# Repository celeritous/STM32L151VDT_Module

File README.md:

# STM32L151VDT_Module
This repository is for an STM32L151/152 Cortex M3 32bit low power ARM  processor module. The design supports any of the STM32L151 or 152 processors in the QFP100 package. It is designed primarily for battery powered applications. 

The design is in KiCad and is released under the CERN OHL Ver 1.2 It is on a 50mm x 50mm 4 layer PCB with two 38 Pin dual row 100mil headers for user power and IO. There is no on-board voltage regulation so the user must supply regulated 1.8V-3.3V power to the board. Voltages in excess of this may damage the board. The board may operate as low as 1.65V but not all peripherals will operate at this voltage and full clock speed maynot be supported. The processor is capable of internal cclock speeds of up to 32MHz. 

Features include a USB FS port that can function as host or client as well as and optional uSD card slot and ESP-07 serial WiFi Module. The uSD card slot and WiFi module may be independently powered down by the processor to reduce power consumption. 

Along with the hardware design, the repository also contains a sample STM32CubeMX pin assignemt project file and a sample Atollic TrueStudio project file generated by the STM32CubeMX project file.

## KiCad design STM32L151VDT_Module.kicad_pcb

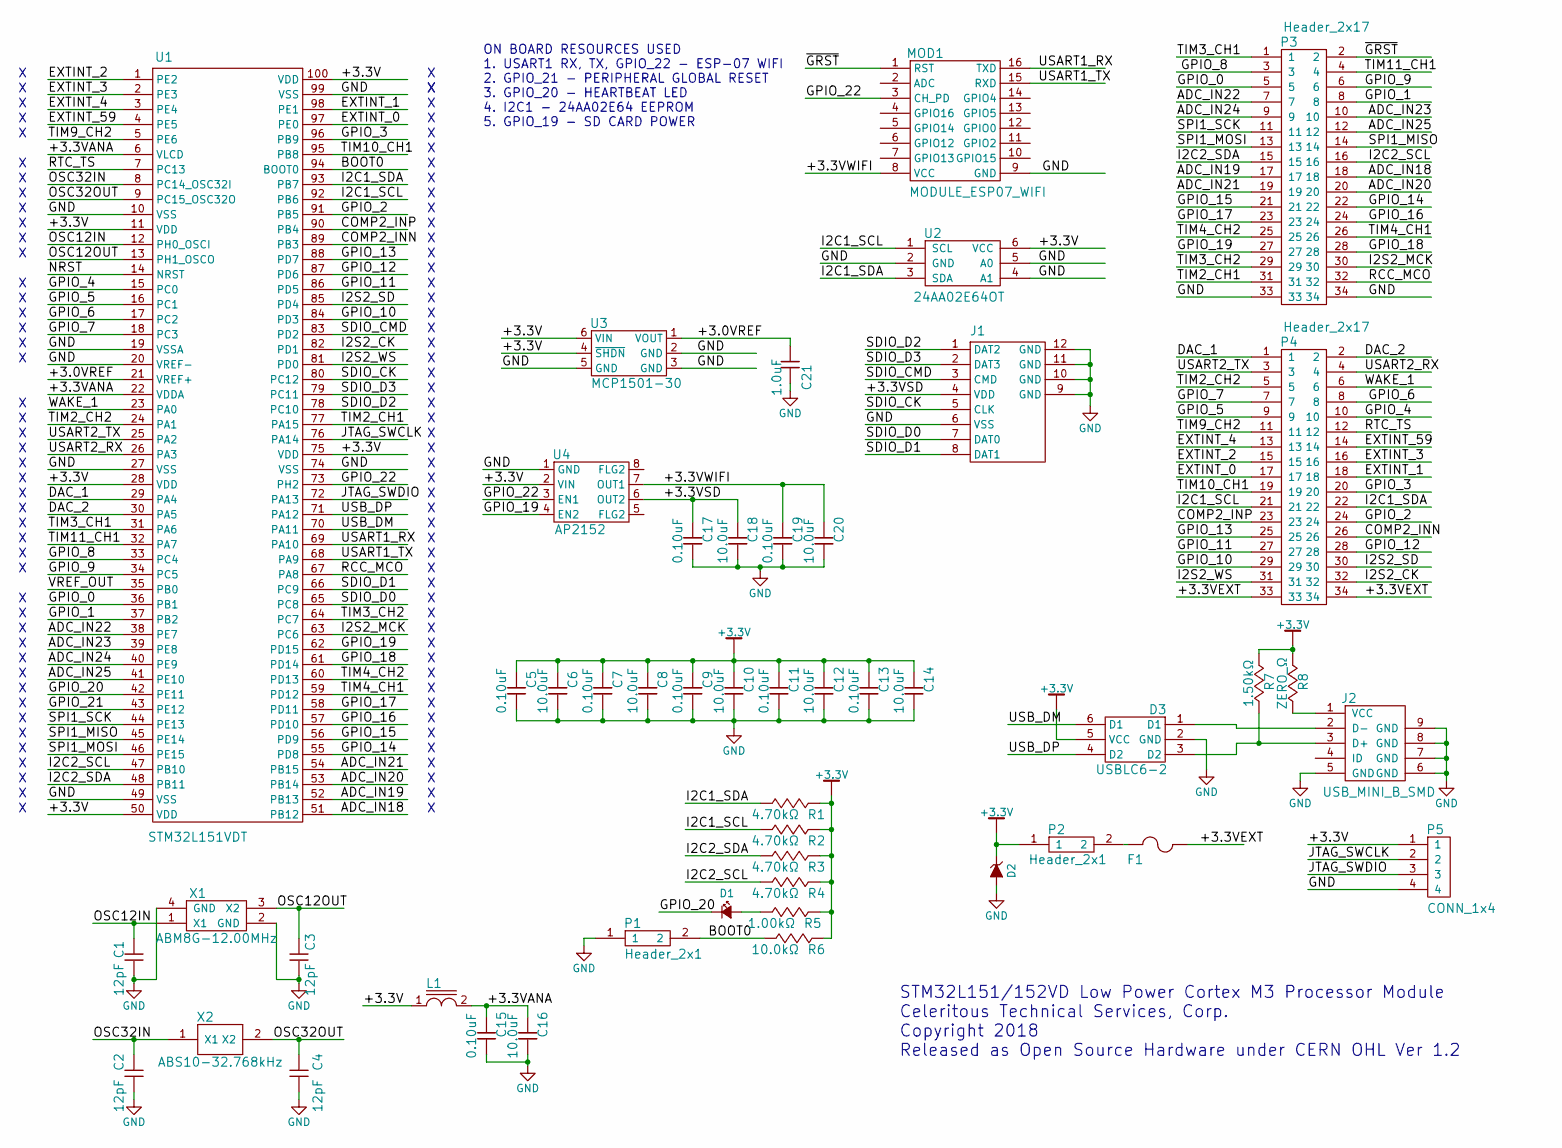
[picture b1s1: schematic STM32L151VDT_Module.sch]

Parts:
C1, C2, C3, C4: 12pF; P0603
C5, C7, C9, C11, C13, C15, C17, C19: 0.10uF; P0603
C6, C8, C10, C12, C14, C16, C18, C20: 10.0uF; P0603
C21: 1.0uF; P0603
D1: Led_Small; D0805
D2: SMLJ33ABCT; SOD128
D3: USBLC6-2; SOT23-6
F1: FUSE_PTC_.5A_33V; P1812
J1: SOCKET_MICRO_SD_SMT_3M; CONN_SDMICRO_3M
J2: USB_MINI_B_SMD; CONN_USB_UX60-MB
L1: FERRITE_BEAD; P0603
MOD1: MODULE_ESP07_WIFI
P1, P2: Header_2x1; Header_2x1_Shrouded_100mil
P3, P4: Header_2x17; Header_2x17_Shrouded_100mil
P5: CONN_1x4; Connector_1x4_100mil_TH
R1, R2, R3, R4: 4.70kΩ; P0603
R5: 1.00kΩ; P0603
R6: 10.0kΩ; P0603
R7: 1.50kΩ; P0603
R8: ZERO_Ω; P0603
U1: STM32L151VDT; QFP_100_14X14_0.5
U2: 24AA02E64OT; SOT23-6
U3: MCP1501-30; SOT23-6
U4: AP2152; SOIC_8
X1: ABM8G-12.00MHz; XTAL_3.2X2.5
X2: ABS10-32.768kHz; XTAL_1.8X4.9mm

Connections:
+3.3V: C5.1, C6.1, C7.1, C8.1, C9.1, C10.1, C11.1, C12.1, C13.1, C14.1, D2.K, D3.5 (VCC), L1.1, P2.1, P5.1, R1.2, R2.2, R3.2, R4.2, R5.2, R6.2, R7.1, R8.1, U1.11 (VDD), U1.28 (VDD), U1.50 (VDD), U1.75 (VDD), U1.100 (VDD), U2.6 (VCC), U3.4 (~SHDN), U3.6 (VIN), U4.2 (VIN)
/+3.0VREF: C21.1, U1.21 (VREF+), U3.1 (VOUT)
/+3.3VANA: C15.1, C16.1, L1.2, U1.6 (VLCD), U1.22 (VDDA)
/+3.3VEXT: F1.2, P4.33, P4.34
/+3.3VSD: C17.1, C18.1, J1.4 (VDD), U4.6 (OUT2)
/+3.3VWIFI: C19.1, C20.1, MOD1.8 (VCC), U4.7 (OUT1)
/ADC_IN18: P3.18, U1.51 (PB12)
/ADC_IN19: P3.17, U1.52 (PB13)
/ADC_IN20: P3.20, U1.53 (PB14)
/ADC_IN21: P3.19, U1.54 (PB15)
/ADC_IN22: P3.7, U1.38 (PE7)
/ADC_IN23: P3.10, U1.39 (PE8)
/ADC_IN24: P3.9, U1.40 (PE9)
/ADC_IN25: P3.12, U1.41 (PE10)
/BOOT0: P1.2, R6.1, U1.94 (BOOT0)
/COMP2_INN: P4.26, U1.89 (PB3)
/COMP2_INP: P4.23, U1.90 (PB4)
/DAC_1: P4.1, U1.29 (PA4)
/DAC_2: P4.2, U1.30 (PA5)
/EXTINT_0: P4.17, U1.97 (PE0)
/EXTINT_1: P4.18, U1.98 (PE1)
/EXTINT_2: P4.15, U1.1 (PE2)
/EXTINT_3: P4.16, U1.2 (PE3)
/EXTINT_4: P4.13, U1.3 (PE4)
/EXTINT_59: P4.14, U1.4 (PE5)
/GPIO_0: P3.5, U1.36 (PB1)
/GPIO_1: P3.8, U1.37 (PB2)
/GPIO_2: P4.24, U1.91 (PB5)
/GPIO_3: P4.20, U1.96 (PB9)
/GPIO_4: P4.10, U1.15 (PC0)
/GPIO_5: P4.9, U1.16 (PC1)
/GPIO_6: P4.8, U1.17 (PC2)
/GPIO_7: P4.7, U1.18 (PC3)
/GPIO_8: P3.3, U1.33 (PC4)
/GPIO_9: P3.6, U1.34 (PC5)
/GPIO_10: P4.29, U1.84 (PD3)
/GPIO_11: P4.27, U1.86 (PD5)
/GPIO_12: P4.28, U1.87 (PD6)
/GPIO_13: P4.25, U1.88 (PD7)
/GPIO_14: P3.22, U1.55 (PD8)
/GPIO_15: P3.21, U1.56 (PD9)
/GPIO_16: P3.24, U1.57 (PD10)
/GPIO_17: P3.23, U1.58 (PD11)
/GPIO_18: P3.28, U1.61 (PD14)
/GPIO_19: P3.27, U1.62 (PD15), U4.4 (EN2)
/GPIO_20: D1.K, U1.42 (PE11)
/GPIO_22: MOD1.3 (CH_PD), U1.73 (PH2), U4.3 (EN1)
/I2C1_SCL: P4.21, R2.1, U1.92 (PB6), U2.1 (SCL)
/I2C1_SDA: P4.22, R1.1, U1.93 (PB7), U2.3 (SDA)
/I2C2_SCL: P3.16, R4.1, U1.47 (PB10)
/I2C2_SDA: P3.15, R3.1, U1.48 (PB11)
/I2S2_CK: P4.32, U1.82 (PD1)
/I2S2_MCK: P3.30, U1.63 (PC6)
/I2S2_SD: P4.30, U1.85 (PD4)
/I2S2_WS: P4.31, U1.81 (PD0)
/JTAG_SWCLK: P5.2, U1.76 (PA14)
/JTAG_SWDIO: P5.3, U1.72 (PA13)
/OSC12IN: C1.1, U1.12 (PH0_OSCI), X1.1 (X1)
/OSC12OUT: C3.1, U1.13 (PH1_OSCO), X1.3 (X2)
/OSC32IN: C2.1, U1.8 (PC14_OSC32I), X2.1 (X1)
/OSC32OUT: C4.1, U1.9 (PC15_OSC32O), X2.2 (X2)
/RCC_MCO: P3.32, U1.67 (PA8)
/RTC_TS: P4.12, U1.7 (PC13)
/SDIO_CK: J1.5 (CLK), U1.80 (PC12)
/SDIO_CMD: J1.3 (CMD), U1.83 (PD2)
/SDIO_D0: J1.7 (DAT0), U1.65 (PC8)
/SDIO_D1: J1.8 (DAT1), U1.66 (PC9)
/SDIO_D2: J1.1 (DAT2), U1.78 (PC10)
/SDIO_D3: J1.2 (DAT3), U1.79 (PC11)
/SPI1_MISO: P3.14, U1.45 (PE14)
/SPI1_MOSI: P3.13, U1.46 (PE15)
/SPI1_SCK: P3.11, U1.44 (PE13)
/TIM2_CH1: P3.31, U1.77 (PA15)
/TIM2_CH2: P4.5, U1.24 (PA1)
/TIM3_CH1: P3.1, U1.31 (PA6)
/TIM3_CH2: P3.29, U1.64 (PC7)
/TIM4_CH1: P3.26, U1.59 (PD12)
/TIM4_CH2: P3.25, U1.60 (PD13)
/TIM9_CH2: P4.11, U1.5 (PE6)
/TIM10_CH1: P4.19, U1.95 (PB8)
/TIM11_CH1: P3.4, U1.32 (PA7)
/USART1_RX: MOD1.16 (TXD), U1.69 (PA10)
/USART1_TX: MOD1.15 (RXD), U1.68 (PA9)
/USART2_RX: P4.4, U1.26 (PA3)
/USART2_TX: P4.3, U1.25 (PA2)
/USB_DM: D3.6 (D1), U1.70 (PA11)
/USB_DP: D3.4 (D2), U1.71 (PA12)
/WAKE_1: P4.6, U1.23 (PA0)
/~GRST: MOD1.1 (RST), P3.2
GND: C1.2, C2.2, C3.2, C4.2, C5.2, C6.2, C7.2, C8.2, C9.2, C10.2, C11.2, C12.2, C13.2, C14.2, C15.2, C16.2, C17.2, C18.2, C19.2, C20.2, C21.2, D2.A, D3.2 (GND), J1.6 (VSS), J1.9 (GND), J1.10 (GND), J1.11 (GND), J1.12 (GND), J2.5 (GND), J2.6 (GND), J2.7 (GND), J2.8 (GND), J2.9 (GND), MOD1.9 (GND), P1.1, P3.33, P3.34, P5.4, U1.10 (VSS), U1.19 (VSSA), U1.20 (VREF-), U1.27 (VSS), U1.49 (VSS), U1.74 (VSS), U1.99 (VSS), U2.2 (GND), U2.4 (A1), U2.5 (A0), U3.2 (GND), U3.3 (GND), U3.5 (GND), U4.1 (GND), X1.2 (GND), X1.4 (GND)
unnamed: D1.A, R5.1
unnamed: D3.1 (D1), J2.2 (D-)
unnamed: D3.3 (D2), J2.3 (D+), R7.2
unnamed: F1.1, P2.2
unnamed: J2.1 (VCC), R8.2

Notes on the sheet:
ON BOARD RESOURCES USED 1. USART1 RX, TX, GPIO_22 - ESP-07 WIFI 2. GPIO_21 - PERIPHERAL GLOBAL RESET 3. GPIO_20 - HEARTBEAT LED 4. I2C1 - 24AA02E64 EEPROM 5. GPIO_19 - SD CARD POWER
STM32L151/152VD Low Power Cortex M3 Processor Module Celeritous Technical Services, Corp. Copyright 2018 Released as Open Source Hardware under CERN OHL Ver 1.2

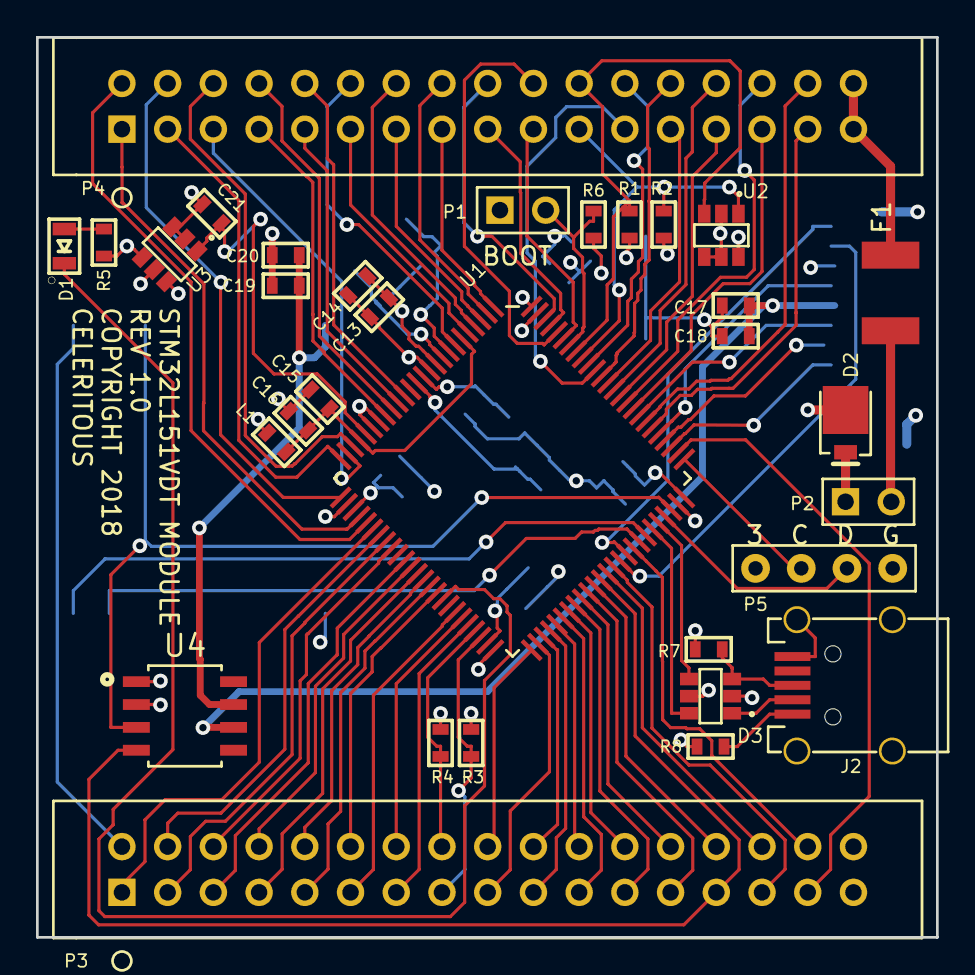
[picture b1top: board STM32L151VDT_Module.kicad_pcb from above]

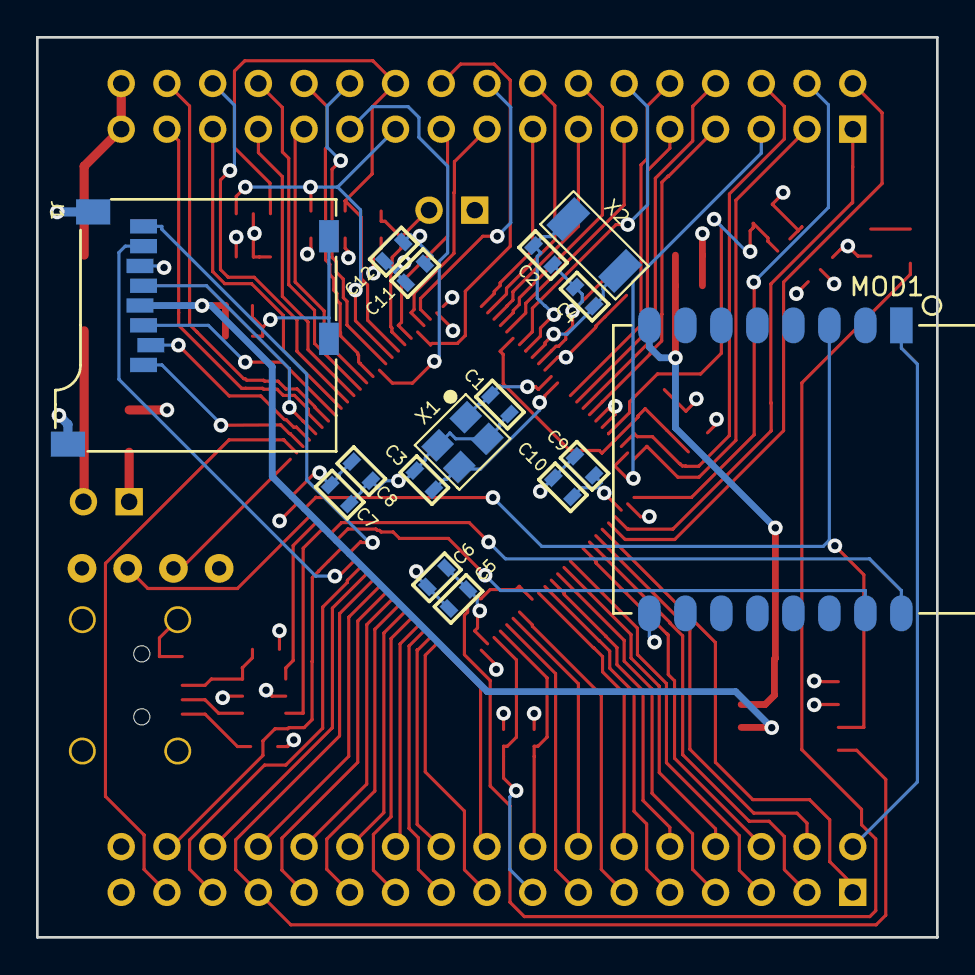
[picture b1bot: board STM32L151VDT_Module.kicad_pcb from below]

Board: 4 copper layers, 50.0 x 50.0 mm, 48 parts (16 on the bottom side), 95 nets.

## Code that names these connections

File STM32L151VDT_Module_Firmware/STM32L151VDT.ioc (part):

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Mcu.Name=STM32L151VDTx
Mcu.Package=LQFP100
Mcu.UserName=STM32L151VDTx
PA0-WKUP1.GPIOParameters=GPIO_Label
PA0-WKUP1.GPIO_Label=WAKE_1
PA0-WKUP1.Mode=SYS_WakeUp0
PA0-WKUP1.Signal=SYS_WKUP1
PA1.Signal=S_TIM2_CH2
PA10.Mode=Asynchronous
PA10.Signal=USART1_RX
PA11.Mode=Device
PA11.Signal=USB_DM
PA12.Mode=Device
PA12.Signal=USB_DP
PA13.Mode=Serial_Wire
PA13.Signal=SYS_JTMS-SWDIO
PA14.Mode=Serial_Wire
PA14.Signal=SYS_JTCK-SWCLK
PA15.Signal=S_TIM2_CH1_ETR
PA2.Mode=Asynchronous
PA2.Signal=USART2_TX
PA3.Mode=Asynchronous
PA3.Signal=USART2_RX
PA4.Signal=COMP_DAC1_group
PA5.Signal=COMP_DAC2_group
PA6.Signal=S_TIM3_CH1
PA7.Signal=S_TIM11_CH1
PA8.Mode=Clock-out
PA8.Signal=RCC_MCO
PA9.Mode=Asynchronous
PA9.Signal=USART1_TX
PB0.GPIOParameters=GPIO_Label
PB0.GPIO_Label=VREF_OUT
PB0.Mode=Voltage_reference
PB0.Signal=SYS_V_REF_OUT
PB1.GPIOParameters=GPIO_Label
PB1.GPIO_Label=GPIO_0
PB1.Signal=GPIO_Input
PB10.Mode=I2C
PB10.Signal=I2C2_SCL
PB11.Mode=I2C
PB11.Signal=I2C2_SDA
PB12.Mode=IN18
PB12.Signal=ADC_IN18
PB13.Mode=IN19
PB13.Signal=ADC_IN19
PB14.Mode=IN20
PB14.Signal=ADC_IN20
PB15.Mode=IN21
PB15.Signal=ADC_IN21
PB2.GPIOParameters=GPIO_Label
PB2.GPIO_Label=GPIO_1
PB2.Signal=GPIO_Input
PB3.GPIOParameters=GPIO_Label
PB3.GPIO_Label=COMP2_INN
PB3.Mode=INM
PB3.Signal=COMP2_INM
PB4.GPIOParameters=GPIO_Label
PB4.GPIO_Label=COMP2_INP
PB4.Mode=INP
PB4.Signal=COMP2_INP
PB5.GPIOParameters=GPIO_Label
PB5.GPIO_Label=GPIO_2
PB5.Signal=GPIO_Input
PB6.Mode=I2C
PB6.Signal=I2C1_SCL
PB7.Mode=I2C
PB7.Signal=I2C1_SDA
PB8.Signal=S_TIM10_CH1
PB9.GPIOParameters=GPIO_Label
PB9.GPIO_Label=GPIO_3
PB9.Signal=GPIO_Input
PC0.GPIOParameters=GPIO_Label
PC0.GPIO_Label=GPIO_4
PC0.Signal=GPIO_Input
PC1.GPIOParameters=GPIO_Label
PC1.GPIO_Label=GPIO_5
PC1.Signal=GPIO_Input
PC10.Mode=SD_4_bits_Wide_bus
PC10.Signal=SDIO_D2
PC11.Mode=SD_4_bits_Wide_bus
PC11.Signal=SDIO_D3
PC12.Mode=SD_4_bits_Wide_bus
PC12.Signal=SDIO_CK
PC13-WKUP2.Mode=Timestamp enabled - Input Enabled to TS
PC13-WKUP2.Signal=RTC_TS
PC14-OSC32_IN.Mode=LSE-External-Oscillator
PC14-OSC32_IN.Signal=RCC_OSC32_IN
PC15-OSC32_OUT.Mode=LSE-External-Oscillator
PC15-OSC32_OUT.Signal=RCC_OSC32_OUT
PC2.GPIOParameters=GPIO_Label
PC2.GPIO_Label=GPIO_6
PC2.Signal=GPIO_Input
PC3.GPIOParameters=GPIO_Label
PC3.GPIO_Label=GPIO_7
PC3.Signal=GPIO_Input
PC4.GPIOParameters=GPIO_Label
PC4.GPIO_Label=GPIO_8
PC4.Signal=GPIO_Input
PC5.GPIOParameters=GPIO_Label
PC5.GPIO_Label=GPIO_9
PC5.Signal=GPIO_Input
PC6.Mode=Master_Clock_Activated
PC6.Signal=I2S2_MCK
PC7.Signal=S_TIM3_CH2
PC8.Mode=SD_4_bits_Wide_bus
PC8.Signal=SDIO_D0
PC9.Mode=SD_4_bits_Wide_bus
PC9.Signal=SDIO_D1
PD0.Mode=Half_Duplex_Master
PD0.Signal=I2S2_WS
PD1.Mode=Half_Duplex_Master
PD1.Signal=I2S2_CK
PD10.GPIOParameters=GPIO_Label
PD10.GPIO_Label=GPIO_16
PD10.Signal=GPIO_Input
PD11.GPIOParameters=GPIO_Label
PD11.GPIO_Label=GPIO_17
PD11.Signal=GPIO_Input
PD12.Signal=S_TIM4_CH1
PD13.Signal=S_TIM4_CH2
PD14.GPIOParameters=GPIO_Label
PD14.GPIO_Label=GPIO_18
PD14.Signal=GPIO_Input
PD15.GPIOParameters=GPIO_Label
PD15.GPIO_Label=GPIO_19
PD15.Signal=GPIO_Input
PD2.Mode=SD_4_bits_Wide_bus
PD2.Signal=SDIO_CMD
PD3.GPIOParameters=GPIO_Label
PD3.GPIO_Label=GPIO_10
PD3.Signal=GPIO_Input
PD4.Mode=Half_Duplex_Master
PD4.Signal=I2S2_SD
PD5.GPIOParameters=GPIO_Label
PD5.GPIO_Label=GPIO_11
PD5.Signal=GPIO_Input
PD6.GPIOParameters=GPIO_Label
PD6.GPIO_Label=GPIO_12
PD6.Signal=GPIO_Input
PD7.GPIOParameters=GPIO_Label
PD7.GPIO_Label=GPIO_13
PD7.Signal=GPIO_Input
PD8.GPIOParameters=GPIO_Label
PD8.GPIO_Label=GPIO_14
PD8.Signal=GPIO_Input
PD9.GPIOParameters=GPIO_Label
PD9.GPIO_Label=GPIO_15
PD9.Signal=GPIO_Input
PE0.GPIOParameters=GPIO_Label
PE0.GPIO_Label=EXTINT_0
PE0.Signal=GPXTI0
PE1.GPIOParameters=GPIO_Label
PE1.GPIO_Label=EXTINT_1
PE1.Signal=GPXTI1
PE10.Mode=IN25
PE10.Signal=ADC_IN25
PE11.GPIOParameters=GPIO_Label
PE11.GPIO_Label=GPIO_20
PE11.Signal=GPIO_Input
PE12.GPIOParameters=GPIO_Label
PE12.GPIO_Label=GPIO_21
PE12.Signal=GPIO_Input
PE13.Mode=Full_Duplex_Master
PE13.Signal=SPI1_SCK
PE14.Mode=Full_Duplex_Master
PE14.Signal=SPI1_MISO
PE15.Mode=Full_Duplex_Master
PE15.Signal=SPI1_MOSI
PE2.GPIOParameters=GPIO_Label
PE2.GPIO_Label=EXTINT_2
PE2.Signal=GPXTI2
PE3.GPIOParameters=GPIO_Label
PE3.GPIO_Label=EXTINT_3
PE3.Signal=GPXTI3
PE4.GPIOParameters=GPIO_Label
PE4.GPIO_Label=EXTINT_4
PE4.Signal=GPXTI4
PE5.GPIOParameters=GPIO_Label
PE5.GPIO_Label=EXTINT_59
PE5.Signal=GPXTI5
PE6-WKUP3.Signal=S_TIM9_CH2
PE7.Mode=IN22
PE7.Signal=ADC_IN22
PE8.Mode=IN23
PE8.Signal=ADC_IN23
PE9.Mode=IN24
PE9.Signal=ADC_IN24
PH0-OSC_IN.Mode=HSE-External-Oscillator
PH0-OSC_IN.Signal=RCC_OSC_IN
PH1-OSC_OUT.Mode=HSE-External-Oscillator
PH1-OSC_OUT.Signal=RCC_OSC_OUT
PH2.GPIOParameters=GPIO_Label
PH2.GPIO_Label=GPIO_22
PH2.Signal=GPIO_Input
RCC.HSE_VALUE=12000000
RCC.SYSCLKFreq_VALUE=32000000
RCC.SYSCLKSource=RCC_SYSCLKSOURCE_PLLCLK

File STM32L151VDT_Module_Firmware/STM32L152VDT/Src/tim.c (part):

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    __HAL_RCC_TIM2_CLK_ENABLE();
  
    /**TIM2 GPIO Configuration    
    PA1     ------> TIM2_CH2
    PA15     ------> TIM2_CH1 
    */
    GPIO_InitStruct.Pin = GPIO_PIN_1|GPIO_PIN_15;
    GPIO_InitStruct.Mode = GPIO_MODE_AF_PP;
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    __HAL_RCC_TIM3_CLK_ENABLE();
  
    /**TIM3 GPIO Configuration    
    PA6     ------> TIM3_CH1
    PC7     ------> TIM3_CH2 
    */
    GPIO_InitStruct.Pin = GPIO_PIN_6;
    GPIO_InitStruct.Mode = GPIO_MODE_AF_PP;
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    __HAL_RCC_TIM4_CLK_ENABLE();
  
    /**TIM4 GPIO Configuration    
    PD12     ------> TIM4_CH1
    PD13     ------> TIM4_CH2 
    */
    GPIO_InitStruct.Pin = GPIO_PIN_12|GPIO_PIN_13;
    GPIO_InitStruct.Mode = GPIO_MODE_AF_PP;
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    __HAL_RCC_TIM10_CLK_ENABLE();
  
    /**TIM10 GPIO Configuration    
    PB8     ------> TIM10_CH1 
    */
    GPIO_InitStruct.Pin = GPIO_PIN_8;
    GPIO_InitStruct.Mode = GPIO_MODE_AF_PP;
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
  /* USER CODE END TIM9_MspPostInit 0 */
    /**TIM9 GPIO Configuration    
    PE6-WKUP3     ------> TIM9_CH2 
    */
    GPIO_InitStruct.Pin = GPIO_PIN_6;
    GPIO_InitStruct.Mode = GPIO_MODE_AF_PP;
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  /* USER CODE END TIM11_MspPostInit 0 */
  
    /**TIM11 GPIO Configuration    
    PA7     ------> TIM11_CH1 
    */
    GPIO_InitStruct.Pin = GPIO_PIN_7;
    GPIO_InitStruct.Mode = GPIO_MODE_AF_PP;
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    __HAL_RCC_TIM2_CLK_DISABLE();
  
    /**TIM2 GPIO Configuration    
    PA1     ------> TIM2_CH2
    PA15     ------> TIM2_CH1 
    */
    HAL_GPIO_DeInit(GPIOA, GPIO_PIN_1|GPIO_PIN_15);

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    __HAL_RCC_TIM3_CLK_DISABLE();
  
    /**TIM3 GPIO Configuration    
    PA6     ------> TIM3_CH1
    PC7     ------> TIM3_CH2 
    */
    HAL_GPIO_DeInit(GPIOA, GPIO_PIN_6);

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    __HAL_RCC_TIM4_CLK_DISABLE();
  
    /**TIM4 GPIO Configuration    
    PD12     ------> TIM4_CH1
    PD13     ------> TIM4_CH2 
    */
    HAL_GPIO_DeInit(GPIOD, GPIO_PIN_12|GPIO_PIN_13);

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    __HAL_RCC_TIM10_CLK_DISABLE();
  
    /**TIM10 GPIO Configuration    
    PB8     ------> TIM10_CH1 
    */
    HAL_GPIO_DeInit(GPIOB, GPIO_PIN_8);

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
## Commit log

2018-03-07 Create README.md
    This is an STM32L151/152 low power processor module for QFP100 packaged devices. It is a 50mm x 50mm 4 Layer PCB with two 38 pin 100mil dual row headers. It features an optional uSD card slot and ESP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
    The design is done in KiCad and is released under the CERN Open Hardware License Version 1.2
2018-03-07 STM32L151/152 Processor Module
    This is an STM32L151/152 low power 32bit ARM Cortex M3 processor module. It is designed for use with the QFP100 packaged devices and brings out most IO for external use. A companion STM32CubeMX proje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
    The processor module is on a 50mm x 50mm 4 layer PCB with two 38 pin dual row 100mil headers provided for power and I/O. There is no on-board power regulation so the board must be fed with regulated 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
    Features include a USB FS Port and opt
2018-03-07 Added Sample TrueStudio / CubeMX

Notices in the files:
STM32L151VDT_Module_Firmware/STM32L152VDT/Src/tim.c:
Copyright (c) 2018 STMicroelectronics International N.V.
All rights reserved.
(C) COPYRIGHT STMicroelectronics *****END OF FILE
STM32L151VDT_Module.kicad_pcb:
Released under CERN OHL Ver 1.2
